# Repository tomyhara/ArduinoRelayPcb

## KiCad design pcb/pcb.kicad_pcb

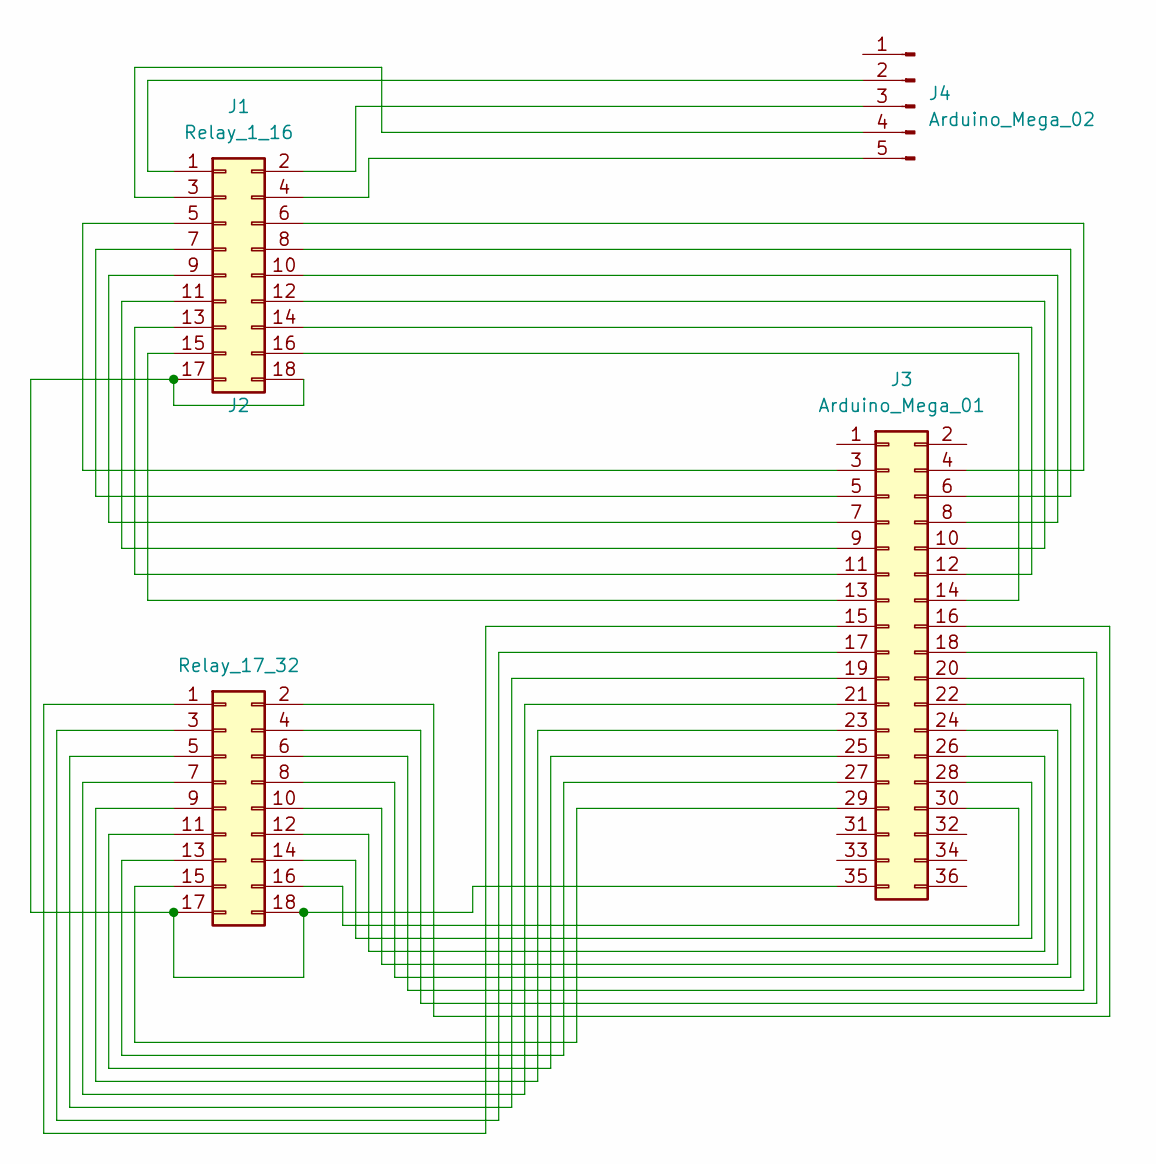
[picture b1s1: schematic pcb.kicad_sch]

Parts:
J1: Relay_1_16; PinHeader_2x09_P2.54mm_Vertical
J2: Relay_17_32; PinHeader_2x09_P2.54mm_Vertical
J3: Arduino_Mega_01; PinHeader_2x18_P2.54mm_Vertical
J4: Arduino_Mega_02; PinHeader_1x05_P2.54mm_Vertical

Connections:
unnamed: J1.1, J4.2
unnamed: J1.2, J4.3
unnamed: J1.3, J4.4
unnamed: J1.4, J4.5
unnamed: J1.5, J3.3
unnamed: J1.6, J3.4
unnamed: J1.7, J3.5
unnamed: J1.8, J3.6
unnamed: J1.9, J3.7
unnamed: J1.10, J3.8
unnamed: J1.11, J3.9
unnamed: J1.12, J3.10
unnamed: J1.13, J3.11
unnamed: J1.14, J3.12
unnamed: J1.15, J3.13
unnamed: J1.16, J3.14
unnamed: J1.17, J1.18, J2.17, J2.18, J3.35
unnamed: J2.1, J3.15
unnamed: J2.2, J3.16
unnamed: J2.3, J3.17
unnamed: J2.4, J3.18
unnamed: J2.5, J3.19
unnamed: J2.6, J3.20
unnamed: J2.7, J3.21
unnamed: J2.8, J3.22
unnamed: J2.9, J3.23
unnamed: J2.10, J3.24
unnamed: J2.11, J3.25
unnamed: J2.12, J3.26
unnamed: J2.13, J3.27
unnamed: J2.14, J3.28
unnamed: J2.15, J3.29
unnamed: J2.16, J3.30

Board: 2 copper layers, 4 parts (0 on the bottom side), 33 nets, no tracks yet.

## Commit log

2022-01-22 Add files
